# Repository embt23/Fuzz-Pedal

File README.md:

# Fuzz-Pedal
Just a quick small kicad fuzz pedal for a society that I joined. Will be changed later to fit the pedal, but it is quite a basic design anyways so I probably wont update the kicad file. Any changes will be basic.

Missing some 3d components but the whole setup should be good

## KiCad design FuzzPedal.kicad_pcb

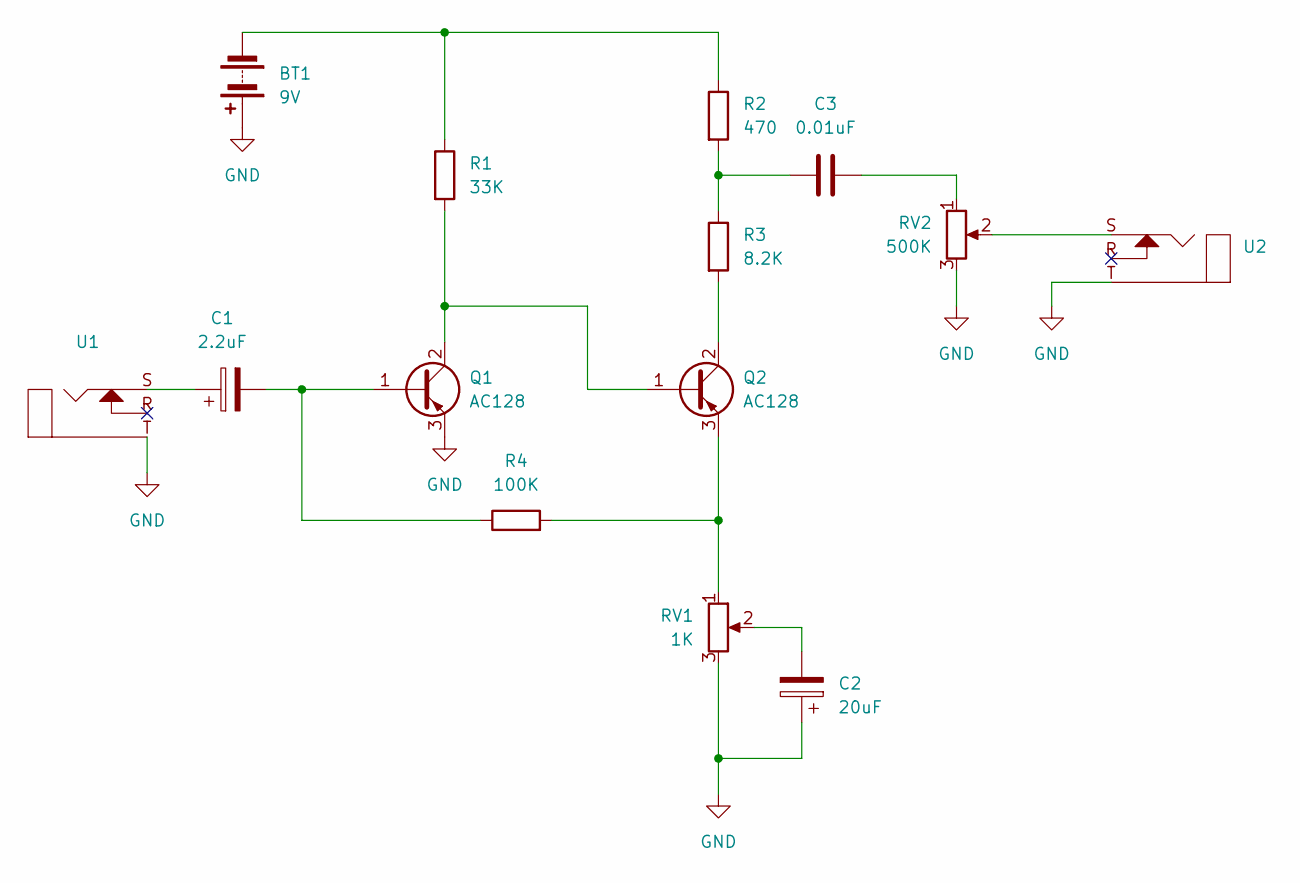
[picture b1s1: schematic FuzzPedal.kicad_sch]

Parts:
BT1: 9V; PinHeader_1x02_P1.00mm_Vertical
C1: 2.2uF; CP_Radial_D5.0mm_P2.00mm
C2: 20uF; CP_Radial_D6.3mm_P2.50mm
C3: 0.01uF; C_Disc_D5.0mm_W2.5mm_P5.00mm
Q1, Q2: AC128; TO-18-3
R1: 33K; R_Axial_DIN0207_L6.3mm_D2.5mm_P7.62mm_Horizontal
R2: 470; R_Axial_DIN0207_L6.3mm_D2.5mm_P7.62mm_Horizontal
R3: 8.2K; R_Axial_DIN0207_L6.3mm_D2.5mm_P7.62mm_Horizontal
R4: 100K; R_Axial_DIN0207_L6.3mm_D2.5mm_P7.62mm_Horizontal
RV1: 1K; Potentiometer_Alpha_RD901F-40-00D_Single_Vertical
RV2: 500K; Potentiometer_Alpha_RD901F-40-00D_Single_Vertical
U1, U2: Jack_3.5mm_CUI_SJ1-3533NG_Horizontal

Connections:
GND: BT1.1 (+), C2.1, Q1.3 (E), RV1.3, RV2.3, U1.T, U2.T
unnamed: BT1.2 (-), R1.1, R2.1
unnamed: C1.1, U1.S
unnamed: C2.2, RV1.2
unnamed: C3.1, R2.2, R3.1
unnamed: C3.2, RV2.1
unnamed: C1.2, Q1.1 (B), R4.1
unnamed: Q1.2 (C), Q2.1 (B), R1.2
unnamed: Q2.2 (C), R3.2
unnamed: Q2.3 (E), R4.2, RV1.1
unnamed: RV2.2, U2.S

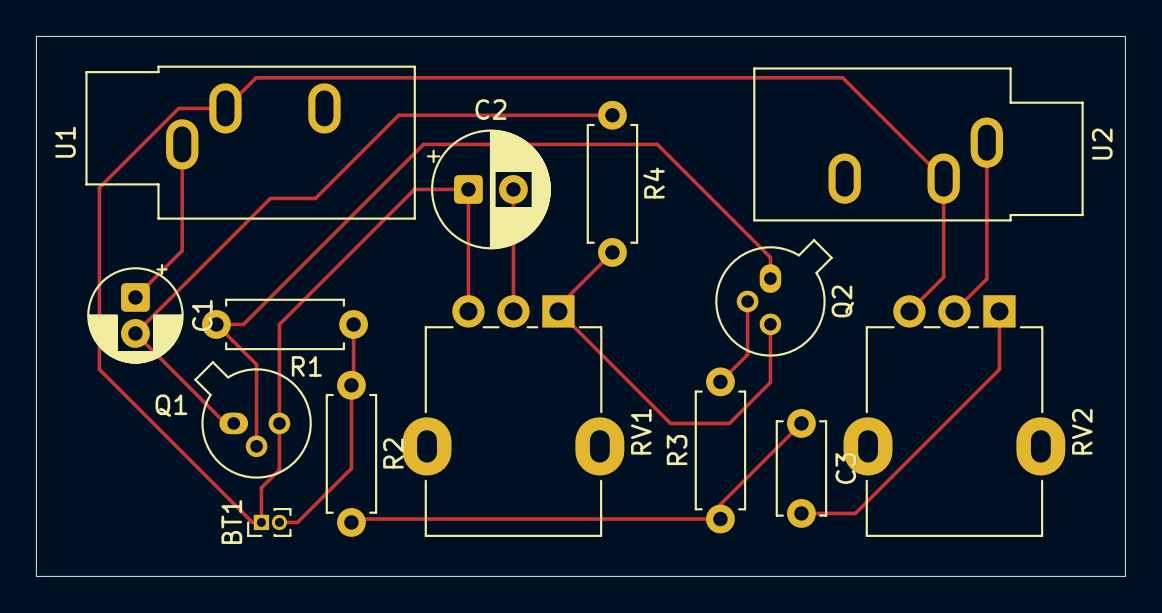
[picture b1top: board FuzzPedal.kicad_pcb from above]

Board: 2 copper layers, 60.5 x 30.0 mm, 14 parts (0 on the bottom side), 11 nets.
